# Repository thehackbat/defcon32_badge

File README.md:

# DEFCON32 Badge

The Hackbat BAdge has been designed specially for DEFCON32. This badge features the ESP32C3 microcontroller with WIFI and Bluetooth. The board also has LEDs, and an OLED Display to show information.

If you received your badge at DEFCON, read [this](#Did-you-receive-your-Hackbat-Badge-at-DEFCON32?)!!

## Microcontroller
The microcontroller used in the Hackbat Badge is the [ESP32-C3](https://www.espressif.com/sites/default/files/documentation/esp32-c3_datasheet_en.pdf) from Espressif. The format used is the WROOM. This microcontroller features a RISC-V single-core processor, WIFI at 2.4GHz IEEE 802.11b/g/n-compliant, Bluetooth LE 5.0, and a bunch of peripherals like SPI, I2C, UART...

This microcontroller can be programmed using either the Arduino IDE or the official [ESP-IDF](https://idf.espressif.com/).

## LEDs

LED are a must in any badge. The Hackbat Badge has 4 smart LEDs, the WS2812. This LED hs a controller integrated so you can choos the color using a serial protocol. The best of these LED is that you can conenct many of them in series, and send different commands to each one. 

## Layout

The layout of the board is designed to looks like an old GAMEBOY, havning 6 push-buttons, and the OLED display. The microcontroller is located in the bottom part of the board, like the USB connector. The backside of the Badge is reserved for a case with three AA cells.

## Did you receive your Hackbat Badge at DEFCON32?

This board have been designed in 2 days to be sure that it will be ready for DEFCON32, but in many cases being the designs fast means errors. If you recevived your Hackbat Badge at DEFCON, the diode D9 is not in its correct place. This diode keep the battery disconnected when the USB is connected, but in the first version of the board this diode is placed in the battery USB side, so since the 5V of the USb are greater than the 4.5 volts of the battery, the USB is conencted directly to the battery. This version have this issue fixed.

## Get Yours

The HackBat Badge is open-source, so you can use the output files to manufacture your own in [JLCPCB](https://jlcpcb.com/?from=controlpath). You just need to compress the `production_files` directory, and upload it to [JLCPCB](https://jlcpcb.com/?from=controlpath). 

Remember to change the Surface Finish to **LeadFree HASL** to make your board ROHS compliant. Also, the original board uses a Black PCB color, so if you want to keep your Hackbat like the original, you can select this color to be sure that the silkscreen is seen correctly.

Then you have to add the PCB Assembly service and upload the [centroid](./kicad/production_files/defcon32_badge-top-pos.csv) file, and the [BOM](./kicad/production_files/bom.csv). 

In a few days, you will receive your board at home.

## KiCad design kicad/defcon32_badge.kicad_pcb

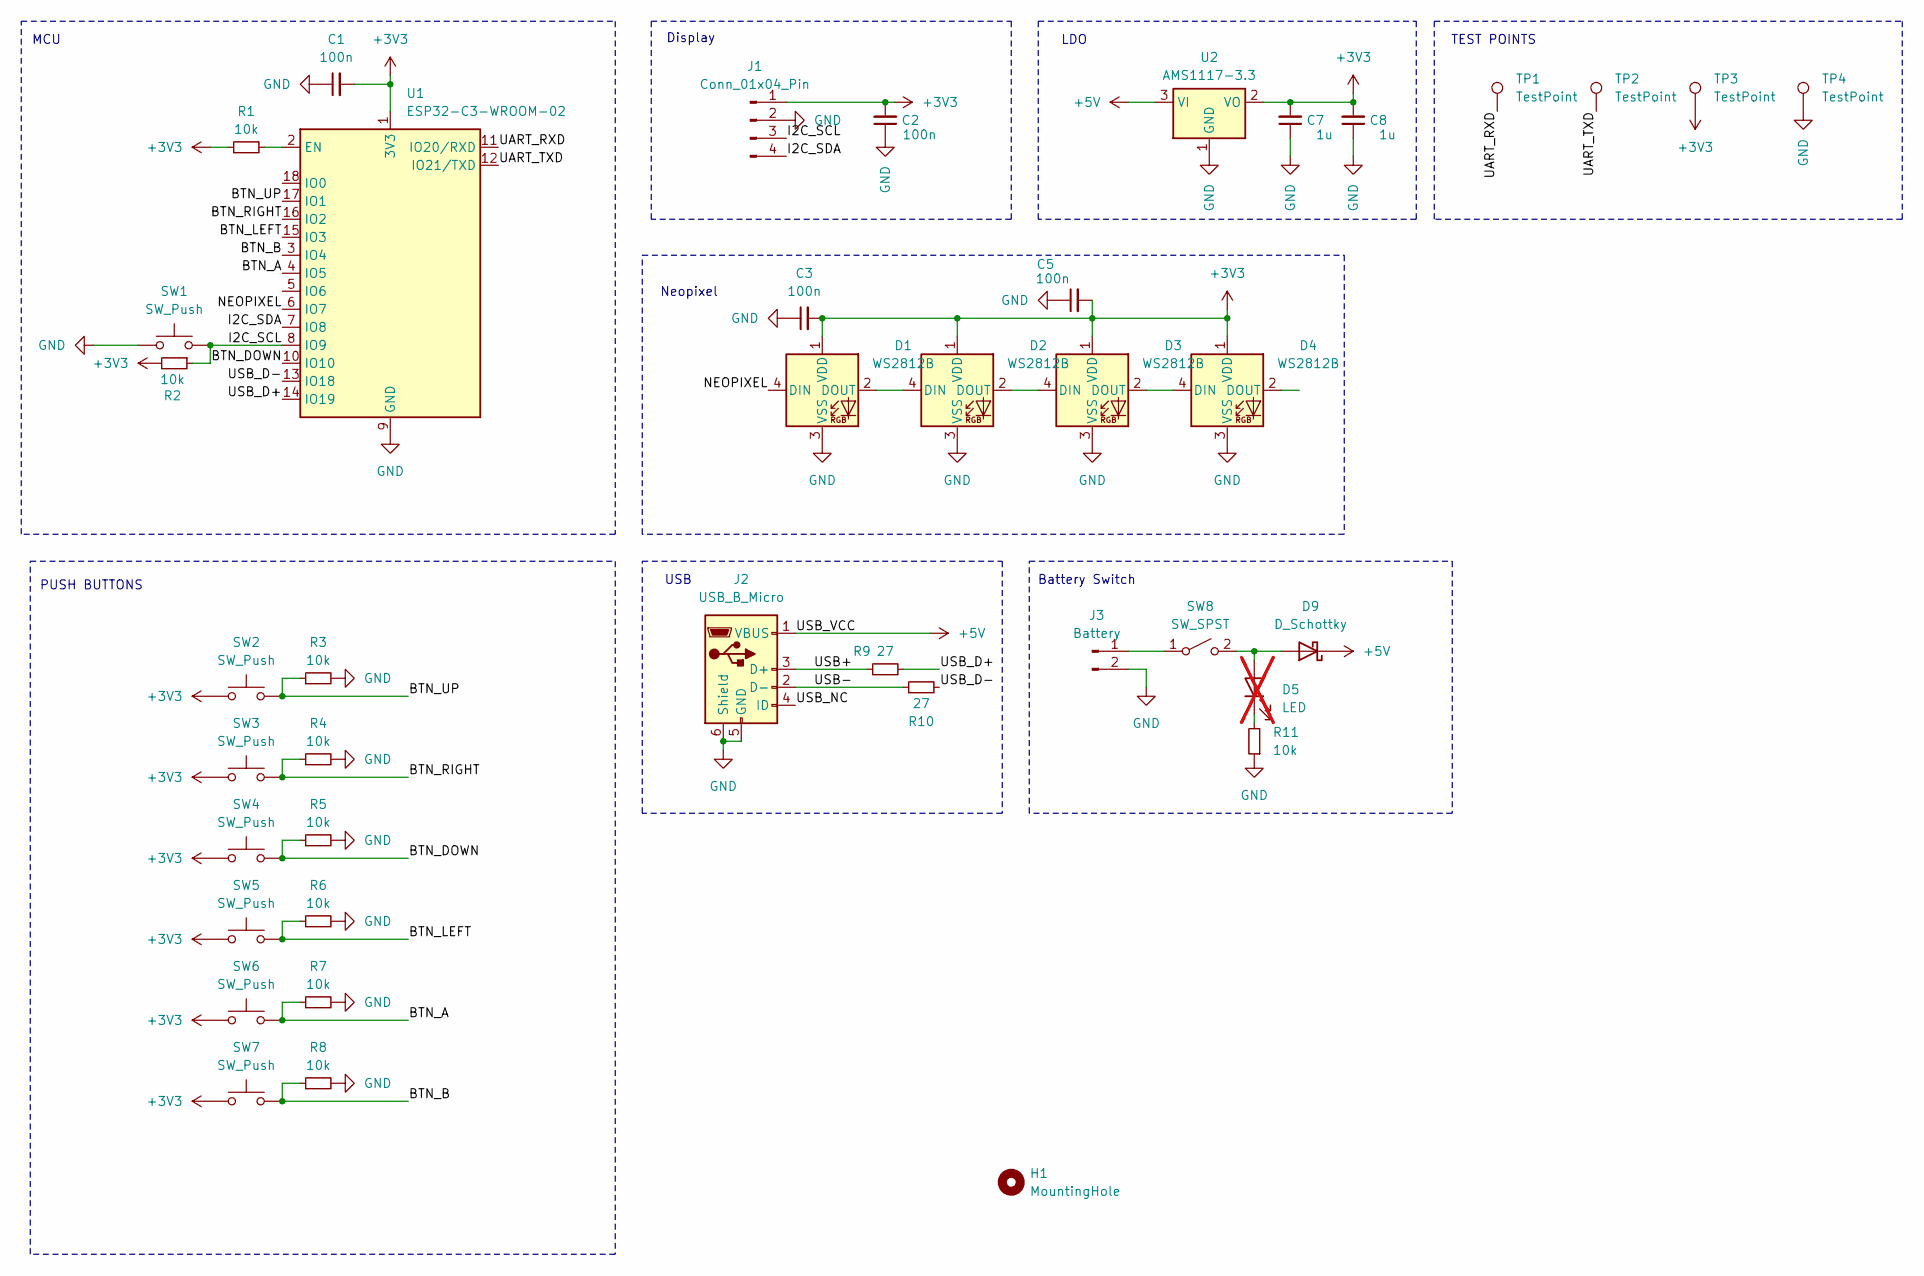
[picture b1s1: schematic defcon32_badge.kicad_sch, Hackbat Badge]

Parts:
C1, C2, C3, C5: 100n; C_0402_1005Metric
C7, C8: 1u; C_0805_2012Metric
D1, D2, D3, D4: WS2812B; LED_WS2812B_PLCC4_5.0x5.0mm_P3.2mm; JLCPCB Part # C2920042
D5: LED; LED_0805_2012Metric; not fitted
D9: D_Schottky; Nexperia_CFP3_SOD-123W; JLCPCB Part # C82544
H1: MountingHole; MountingHole_3.2mm_M3
J1: Conn_01x04_Pin; PinSocket_1x04_P2.54mm_Vertical
J2: USB_B_Micro; USB_Micro-B_Amphenol_10118193-0001LF_Horizontal; JLCPCB Part # C132562
J3: Battery; PinSocket_1x02_P2.54mm_Vertical_SMD_Pin1Left
R1, R2, R3, R4, R5, R6, R7, R8, R11: 10k; R_0402_1005Metric
R9, R10: 27; R_0402_1005Metric
SW1: SW_Push; SW_Push_SPST_NO_Alps_SKRK; JLCPCB Part # C115357
SW2, SW3, SW4, SW5, SW6, SW7: SW_Push; SW_Push_1P1T_NO_6x6mm_H9.5mm; JLCPCB Part # C455109
SW8: SW_SPST; SW_SPDT_CK_JS102011SAQN; JLCPCB Part # C92658
TP1, TP2, TP3, TP4: TestPoint; TestPoint_Pad_D1.0mm
U1: ESP32-C3-WROOM-02; JLCPCB Part # C2934560
U2: AMS1117-3.3; SOT-223-3_TabPin2

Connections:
+3V3: C1.2, C2.2, C3.2, C5.2, C7.2, C8.2, D1.1 (VDD), D2.1 (VDD), D3.1 (VDD), D4.1 (VDD), J1.1, R1.1, R2.2, SW2.1, SW3.1, SW4.1, SW5.1, SW6.1, SW7.1, TP3.1, U1.1 (3V3), U2.2 (VO)
+5V: D9.1 (K), J2.1 (VBUS), U2.3 (VI)
/BTN_A: R7.1, SW6.2, U1.4 (IO5)
/BTN_B: R8.1, SW7.2, U1.3 (IO4)
/BTN_DOWN: R5.1, SW4.2, U1.10 (IO10)
/BTN_LEFT: R6.1, SW5.2, U1.15 (IO3)
/BTN_RIGHT: R4.1, SW3.2, U1.16 (IO2)
/BTN_UP: R3.1, SW2.2, U1.17 (IO1)
/I2C_SCL: J1.3, R2.1, SW1.2, U1.8 (IO9)
/I2C_SDA: J1.4, U1.7 (IO8)
/NEOPIXEL: D1.4 (DIN), U1.6 (IO7)
/UART_RXD: TP1.1, U1.11 (IO20/RXD)
/UART_TXD: TP2.1, U1.12 (IO21/TXD)
/USB+: J2.3 (D+), R9.1
/USB-: J2.2 (D-), R10.1
/USB_D+: R9.2, U1.14 (IO19)
/USB_D-: R10.2, U1.13 (IO18)
/USB_NC: J2.4 (ID)
GND: C1.1, C2.1, C3.1, C5.1, C7.1, C8.1, D1.3 (VSS), D2.3 (VSS), D3.3 (VSS), D4.3 (VSS), J1.2, J2.5 (GND), J2.6 (Shield), J3.2, R3.2, R4.2, R5.2, R6.2, R7.2, R8.2, R11.1, SW1.1, TP4.1, U1.9 (GND), U1.19 (GND), U2.1 (GND)
unnamed: D1.2 (DOUT), D2.4 (DIN)
unnamed: D2.2 (DOUT), D3.4 (DIN)
unnamed: D3.2 (DOUT), D4.4 (DIN)
unnamed: D5.2 (A), D9.2 (A), SW8.2 (B)
unnamed: D5.1 (K), R11.2
unnamed: J3.1, SW8.1 (A)
unnamed: R1.2, U1.2 (EN)

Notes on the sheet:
LDO
Display
USB
MCU
Neopixel
TEST POINTS
PUSH BUTTONS
Battery Switch

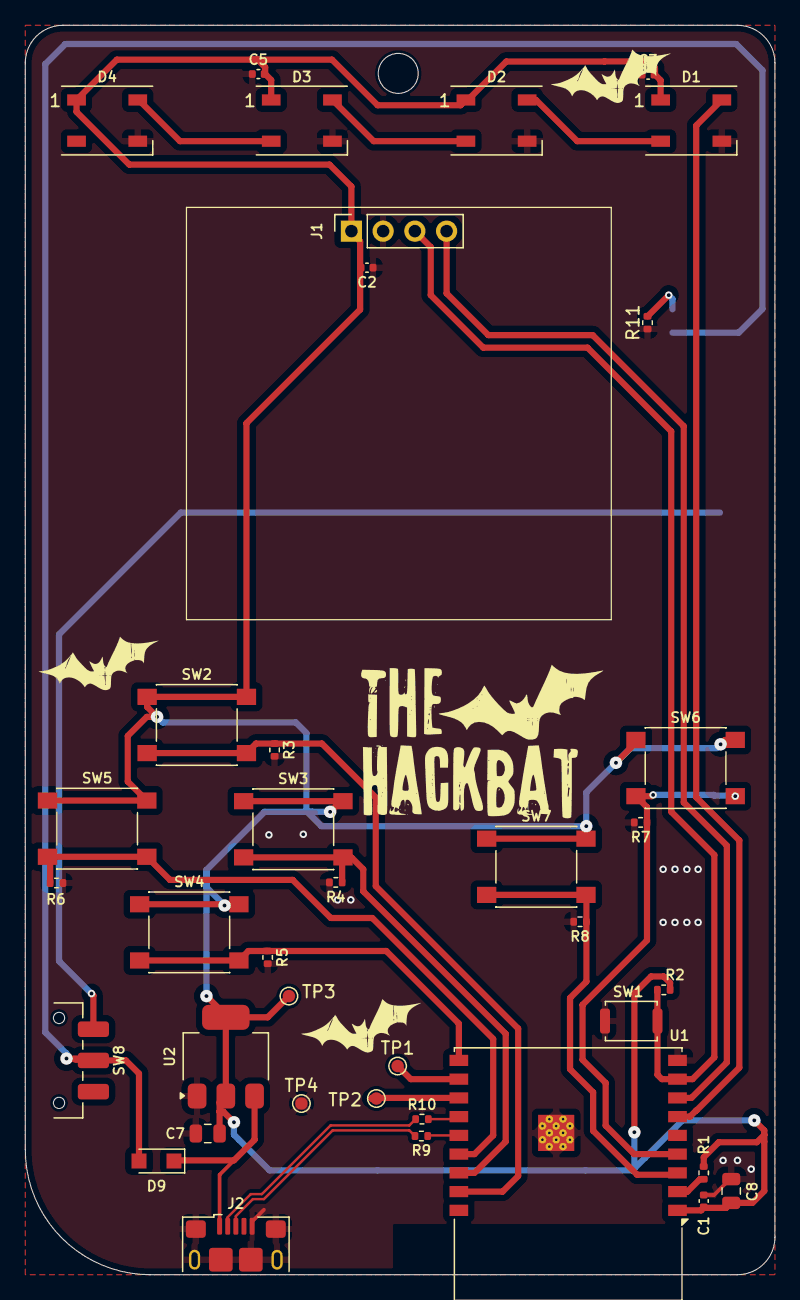
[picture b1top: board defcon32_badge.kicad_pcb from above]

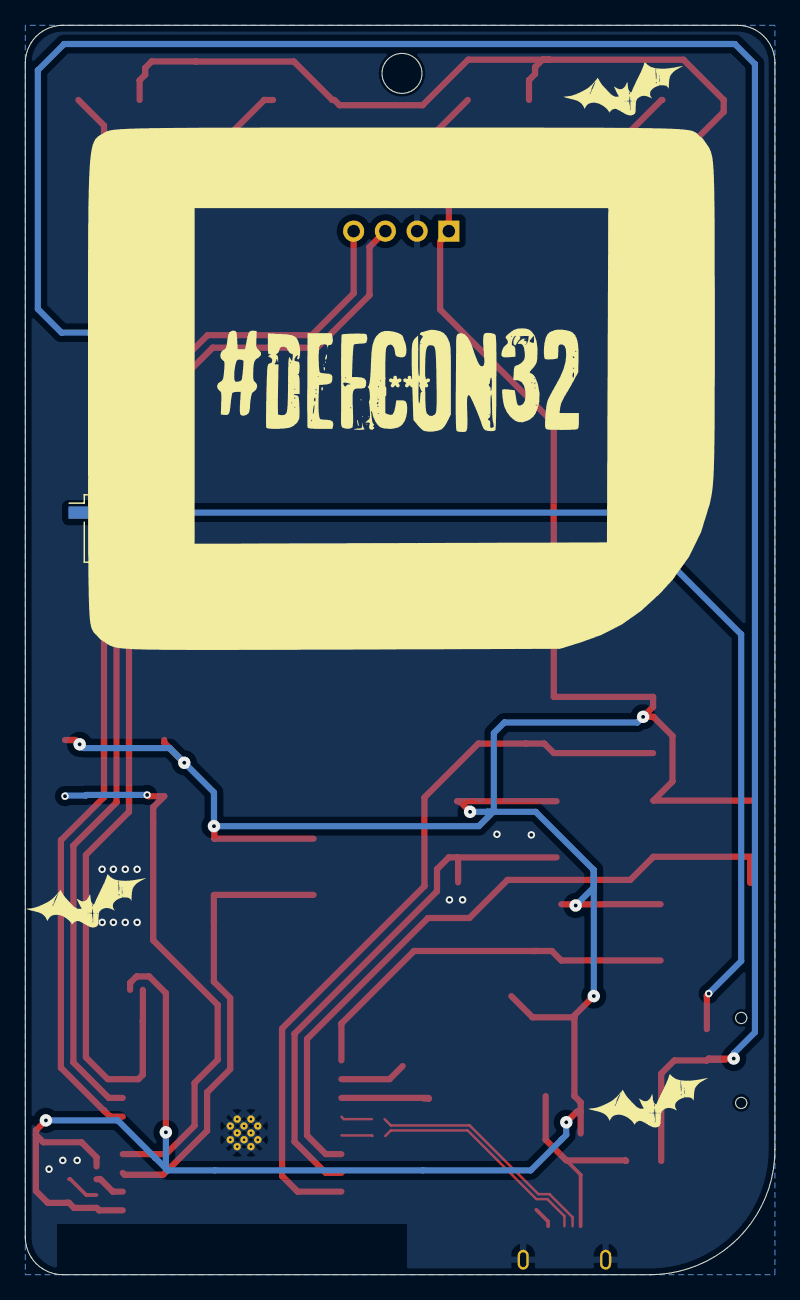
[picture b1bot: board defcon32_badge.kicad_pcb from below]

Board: 2 copper layers, 60.0 x 100.0 mm, 41 parts (2 on the bottom side), 25 nets.

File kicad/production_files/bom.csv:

"Reference","Value","Datasheet","Footprint","Qty","DNP","JLCPCB Part #","JLCPCB Part # "
"C1,C2,C3,C5","100n","~","Capacitor_SMD:C_0402_1005Metric","4","","",""
"C7,C8","1u","~","Capacitor_SMD:C_0805_2012Metric","2","","",""
"D1,D2,D3,D4","WS2812B","https://cdn-shop.adafruit.com/datasheets/WS2812B.pdf","LED_SMD:LED_WS2812B_PLCC4_5.0x5.0mm_P3.2mm","4","","C2920042",""
"D5","LED","~","LED_SMD:LED_0805_2012Metric","1","DNP","",""
"D9","D_Schottky","~","Diode_SMD:Nexperia_CFP3_SOD-123W","1","","C82544",""
"J1","Conn_01x04_Pin","~","Connector_PinSocket_2.54mm:PinSocket_1x04_P2.54mm_Vertical","1","","",""
"J2","USB_B_Micro","~","Connector_USB:USB_Micro-B_Amphenol_10118193-0001LF_Horizontal","1","","C132562",""
"J3","Battery","~","Connector_PinSocket_2.54mm:PinSocket_1x02_P2.54mm_Vertical_SMD_Pin1Left","1","","",""
"R1,R2,R3,R4,R5,R6,R7,R8,R11","10k","~","Resistor_SMD:R_0402_1005Metric","9","","",""
"R9,R10","27","~","Resistor_SMD:R_0402_1005Metric","2","","",""
"SW1","SW_Push","~","Button_Switch_SMD:SW_Push_SPST_NO_Alps_SKRK","1","","C115357",""
"SW2,SW3,SW4,SW5,SW6,SW7","SW_Push","~","Button_Switch_SMD:SW_Push_1P1T_NO_6x6mm_H9.5mm","6","","C455109",""
"SW8","SW_SPST","~","Button_Switch_SMD:SW_SPDT_CK_JS102011SAQN","1",""," C92658",""
"TP1,TP2,TP3,TP4","TestPoint","~","TestPoint:TestPoint_Pad_D1.0mm","4","","",""
"U1","ESP32-C3-WROOM-02","https://www.espressif.com/sites/default/files/documentation/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","RF_Module:ESP32-C3-WROOM-02","1","","C2934560",""
"U2","AMS1117-3.3","http://www.advanced-monolithic.com/pdf/ds1117.pdf","Package_TO_SOT_SMD:SOT-223-3_TabPin2","1","","",""

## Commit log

2024-08-28 uploaded version A of the board
2024-08-30 Create LICENSE
    Added license
